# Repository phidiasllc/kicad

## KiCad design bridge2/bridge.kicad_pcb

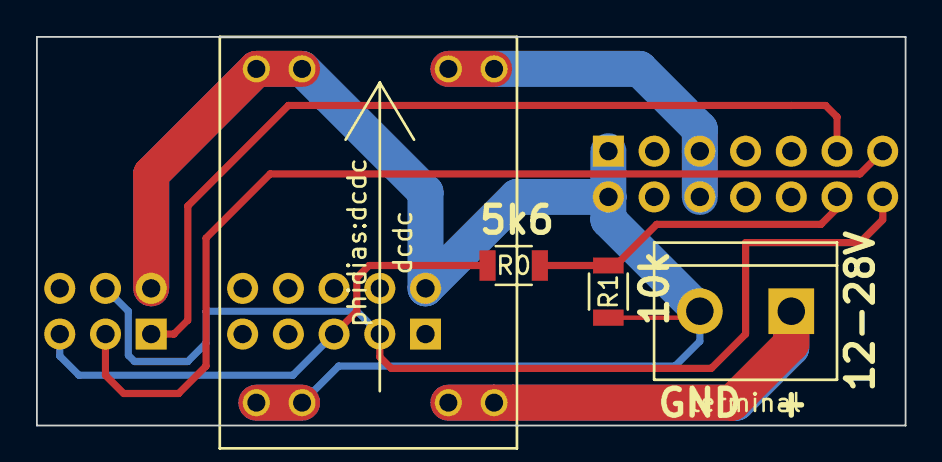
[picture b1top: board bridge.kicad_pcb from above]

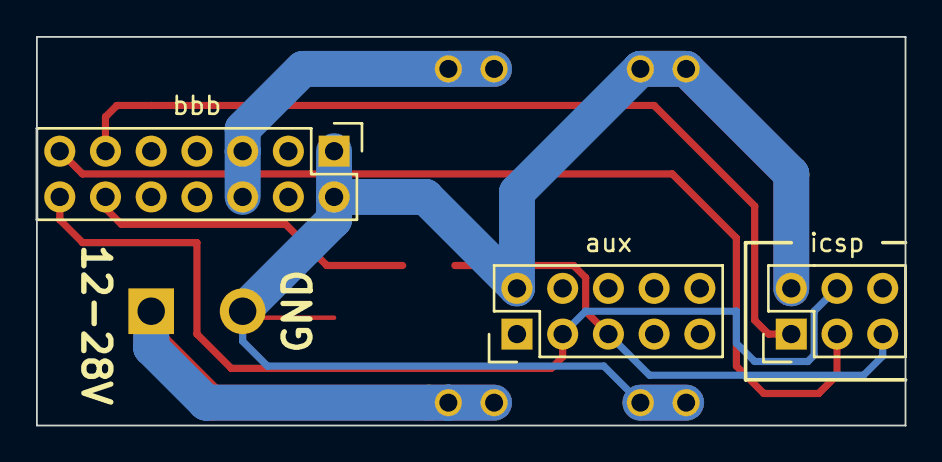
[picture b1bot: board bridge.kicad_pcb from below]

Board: 2 copper layers, 48.3 x 21.6 mm, 7 parts (3 on the bottom side), 8 nets.

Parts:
R0, R1: Resistors_SMD:R_1206; R_1206
aux: Pin_Headers:Pin_Header_Straight_2x05; Pin_Header_Straight_2x05
bbb: Pin_Headers:Pin_Header_Straight_2x07; Pin_Header_Straight_2x07
dcdc: phidias:dcdc; dcdc
icsp: Pin_Headers:Pin_Header_Straight_2x03; Pin_Header_Straight_2x03
terminal: Connect:bornier2; bornier2

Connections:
5v: bbb.5, bbb.6, dcdc.out
24V: dcdc.in, terminal.1
gnd: R1.2, aux.2, bbb.1, bbb.2, dcdc.gnd, icsp.2, terminal.2
miso_3v3: R0.2, R1.1, bbb.12
miso_5v: R0.1, aux.5, icsp.5
mosi: aux.3, bbb.14, icsp.4
reset: bbb.11, icsp.1
sck: bbb.13, icsp.3
